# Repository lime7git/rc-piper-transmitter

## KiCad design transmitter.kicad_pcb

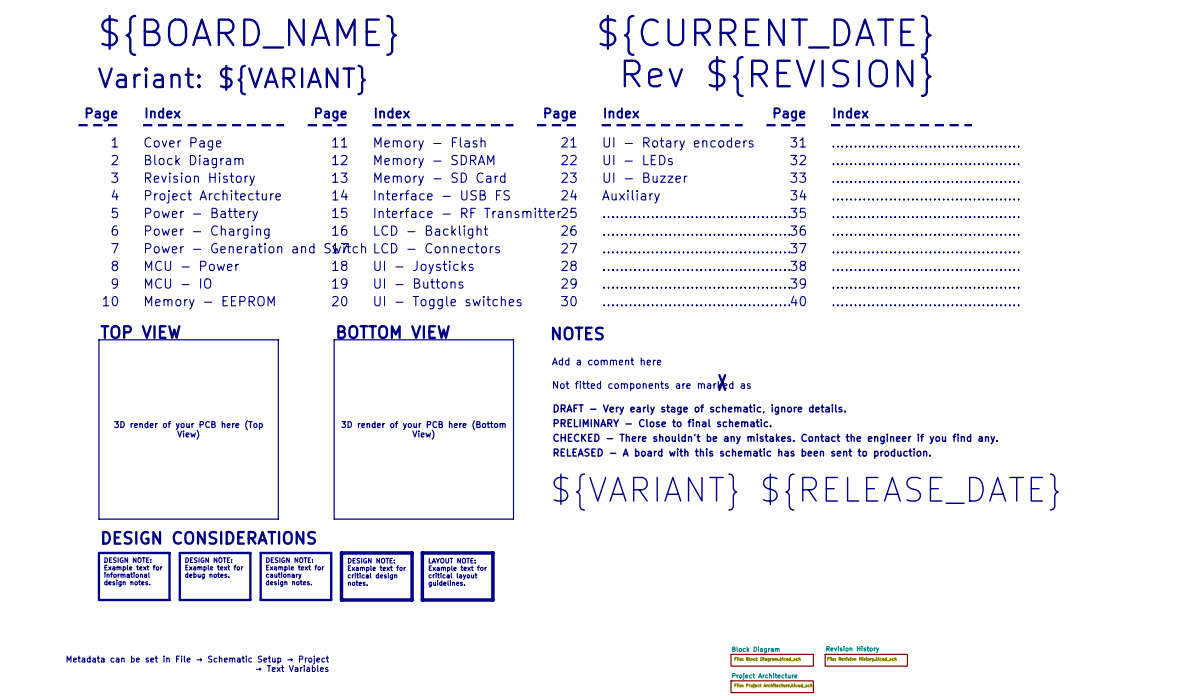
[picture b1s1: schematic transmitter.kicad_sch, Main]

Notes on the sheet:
BOTTOM VIEW
UI - Buzzer
RELEASED - A board with this schematic has been sent to production.
Page
TOP VIEW
Memory - EEPROM
MCU - IO
MCU - Power
LCD - Backlight
Not fitted components are marked as
...........................................
Index
Memory - SD Card
PRELIMINARY - Close to final schematic.
${VARIANT} ${RELEASE_DATE}
Project Architecture
${CURRENT_DATE}
Variant: ${VARIANT}
Rev ${REVISION}
Auxiliary
UI - LEDs
Power - Battery
UI - Buttons
Memory - Flash
LCD - Connectors
Interface - RF Transmitter
${BOARD_NAME}
DRAFT - Very early stage of schematic, ignore details.
Interface - USB FS
Power - Charging
Block Diagram
Add a comment here
UI - Joysticks
UI - Toggle switches
Cover Page
NOTES
Memory - SDRAM
Revision History
CHECKED - There shouldn't be any mistakes. Contact the engineer if you find any.
UI - Rotary encoders

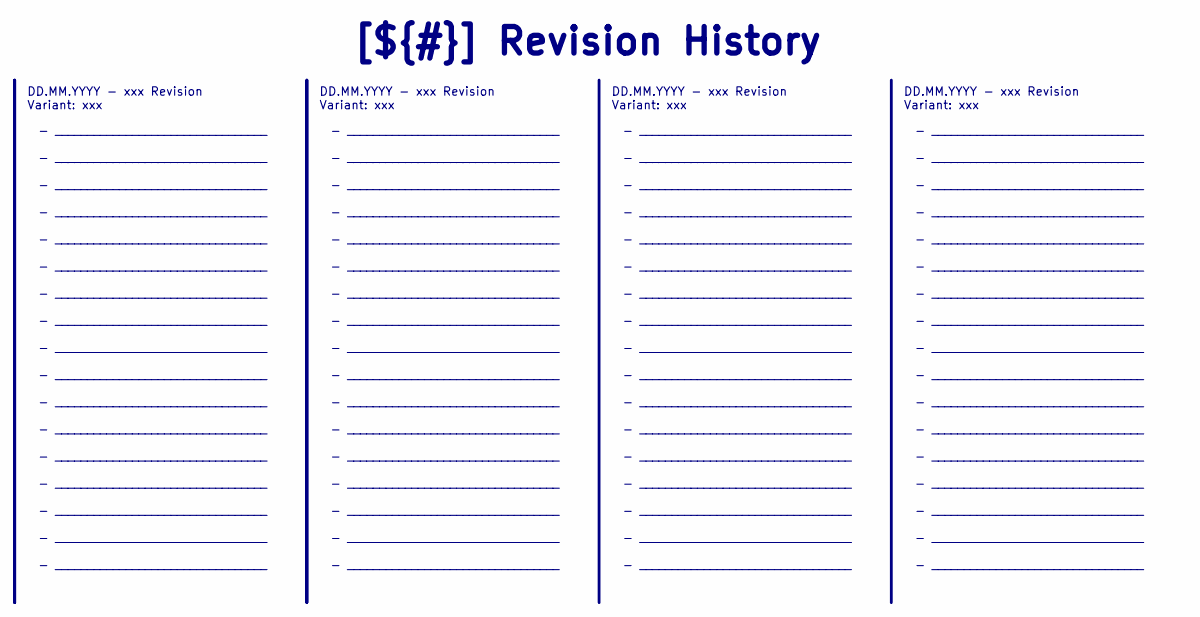
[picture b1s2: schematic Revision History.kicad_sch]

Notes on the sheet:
- _________________________________ - _________________________________ - _________________________________ - _________________________________ - _________________________________ - _________________________________ - _________________________________ - _________________________________ - _________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
DD.MM.YYYY - xxx Revision Variant: xxx
[${#}] ${TITLE}

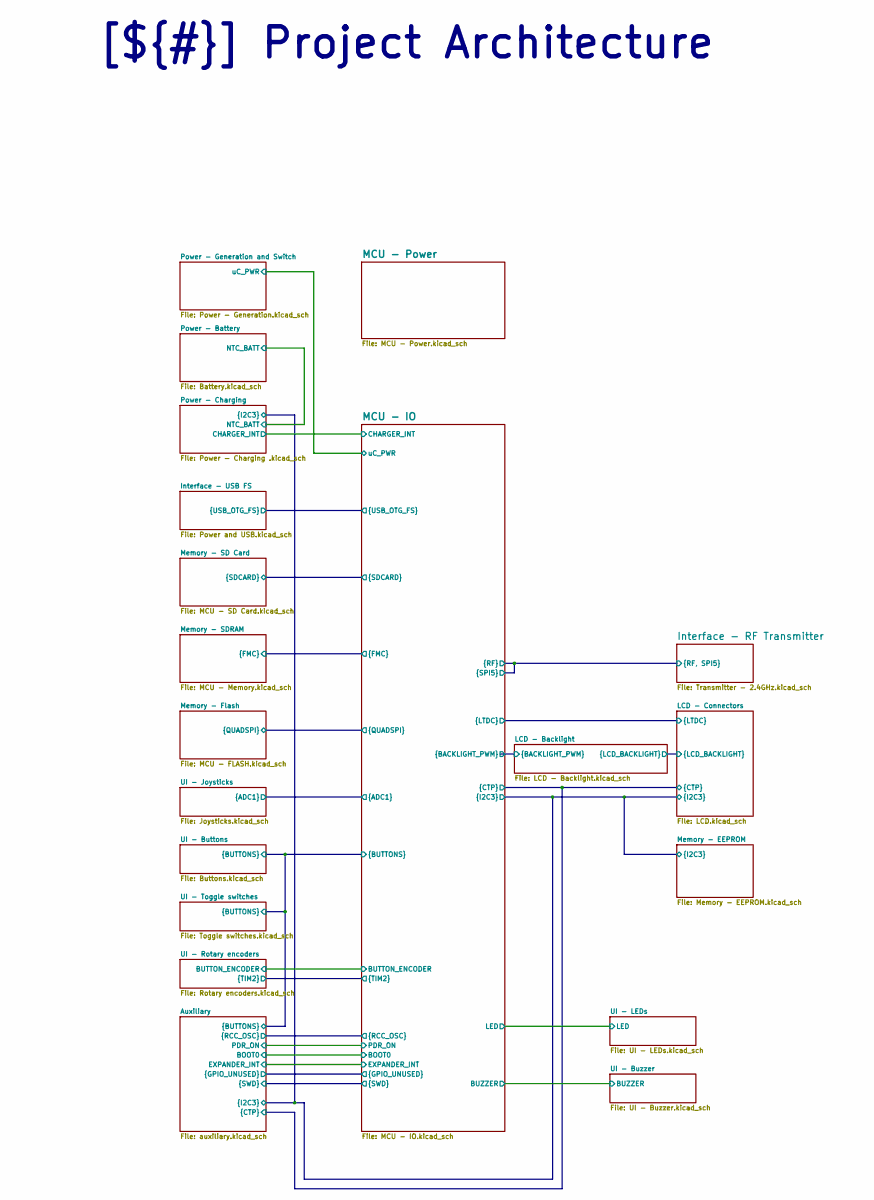
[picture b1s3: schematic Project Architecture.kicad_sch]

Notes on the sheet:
[${#}] ${TITLE}

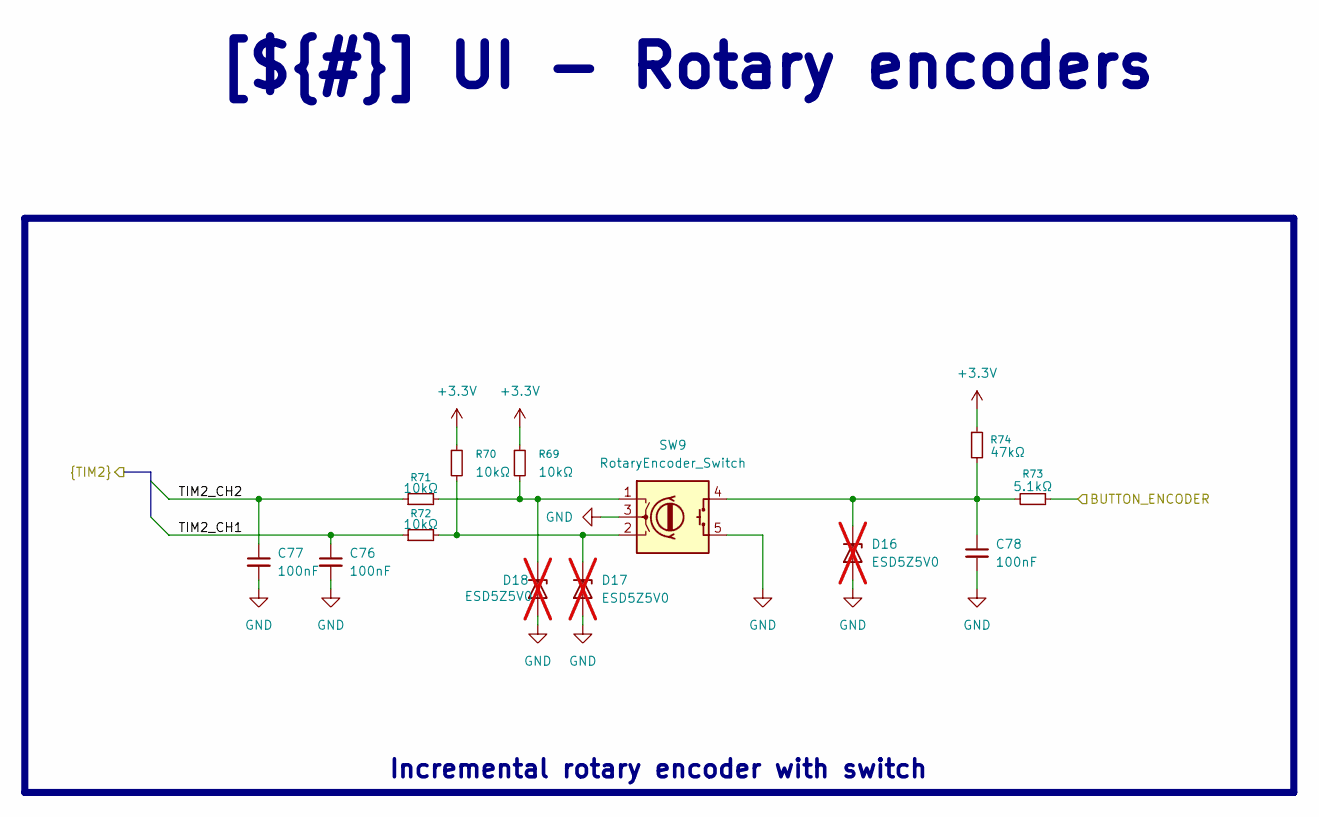
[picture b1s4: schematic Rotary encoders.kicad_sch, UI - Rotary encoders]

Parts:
C76, C77, C78: 100nF; C_0402_1005Metric
D16, D17, D18: ESD5Z5V0; D_SOD-523; not fitted
R69, R70, R71, R72: 10kΩ; R_0402_1005Metric
R73: 5.1kΩ; R_0402_1005Metric
R74: 47kΩ; R_0402_1005Metric
SW9: RotaryEncoder_Switch; JST_PH_B5B-PH-K_1x05_P2.00mm_Vertical

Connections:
+3.3V: R69.1, R70.1, R74.1; also elsewhere on the board
/Project Architecture/MCU - IO/ENC_BUTTON: R73.1; also elsewhere on the board
/Project Architecture/MCU - IO/TIM2_CH1: C76.1, R72.1; also elsewhere on the board
/Project Architecture/MCU - IO/TIM2_CH2: C77.1, R71.1; also elsewhere on the board
GND: C76.2, C77.2, C78.2, D16.2 (A), D17.2 (A), D18.2 (A), SW9.3, SW9.5; also elsewhere on the board
unnamed: C78.1, D16.1 (K), R73.2, R74.2, SW9.4
unnamed: D17.1 (K), R70.2, R72.2, SW9.2
unnamed: D18.1 (K), R69.2, R71.2, SW9.1

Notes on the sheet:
Incremental rotary encoder with switch
[${#}] ${TITLE}

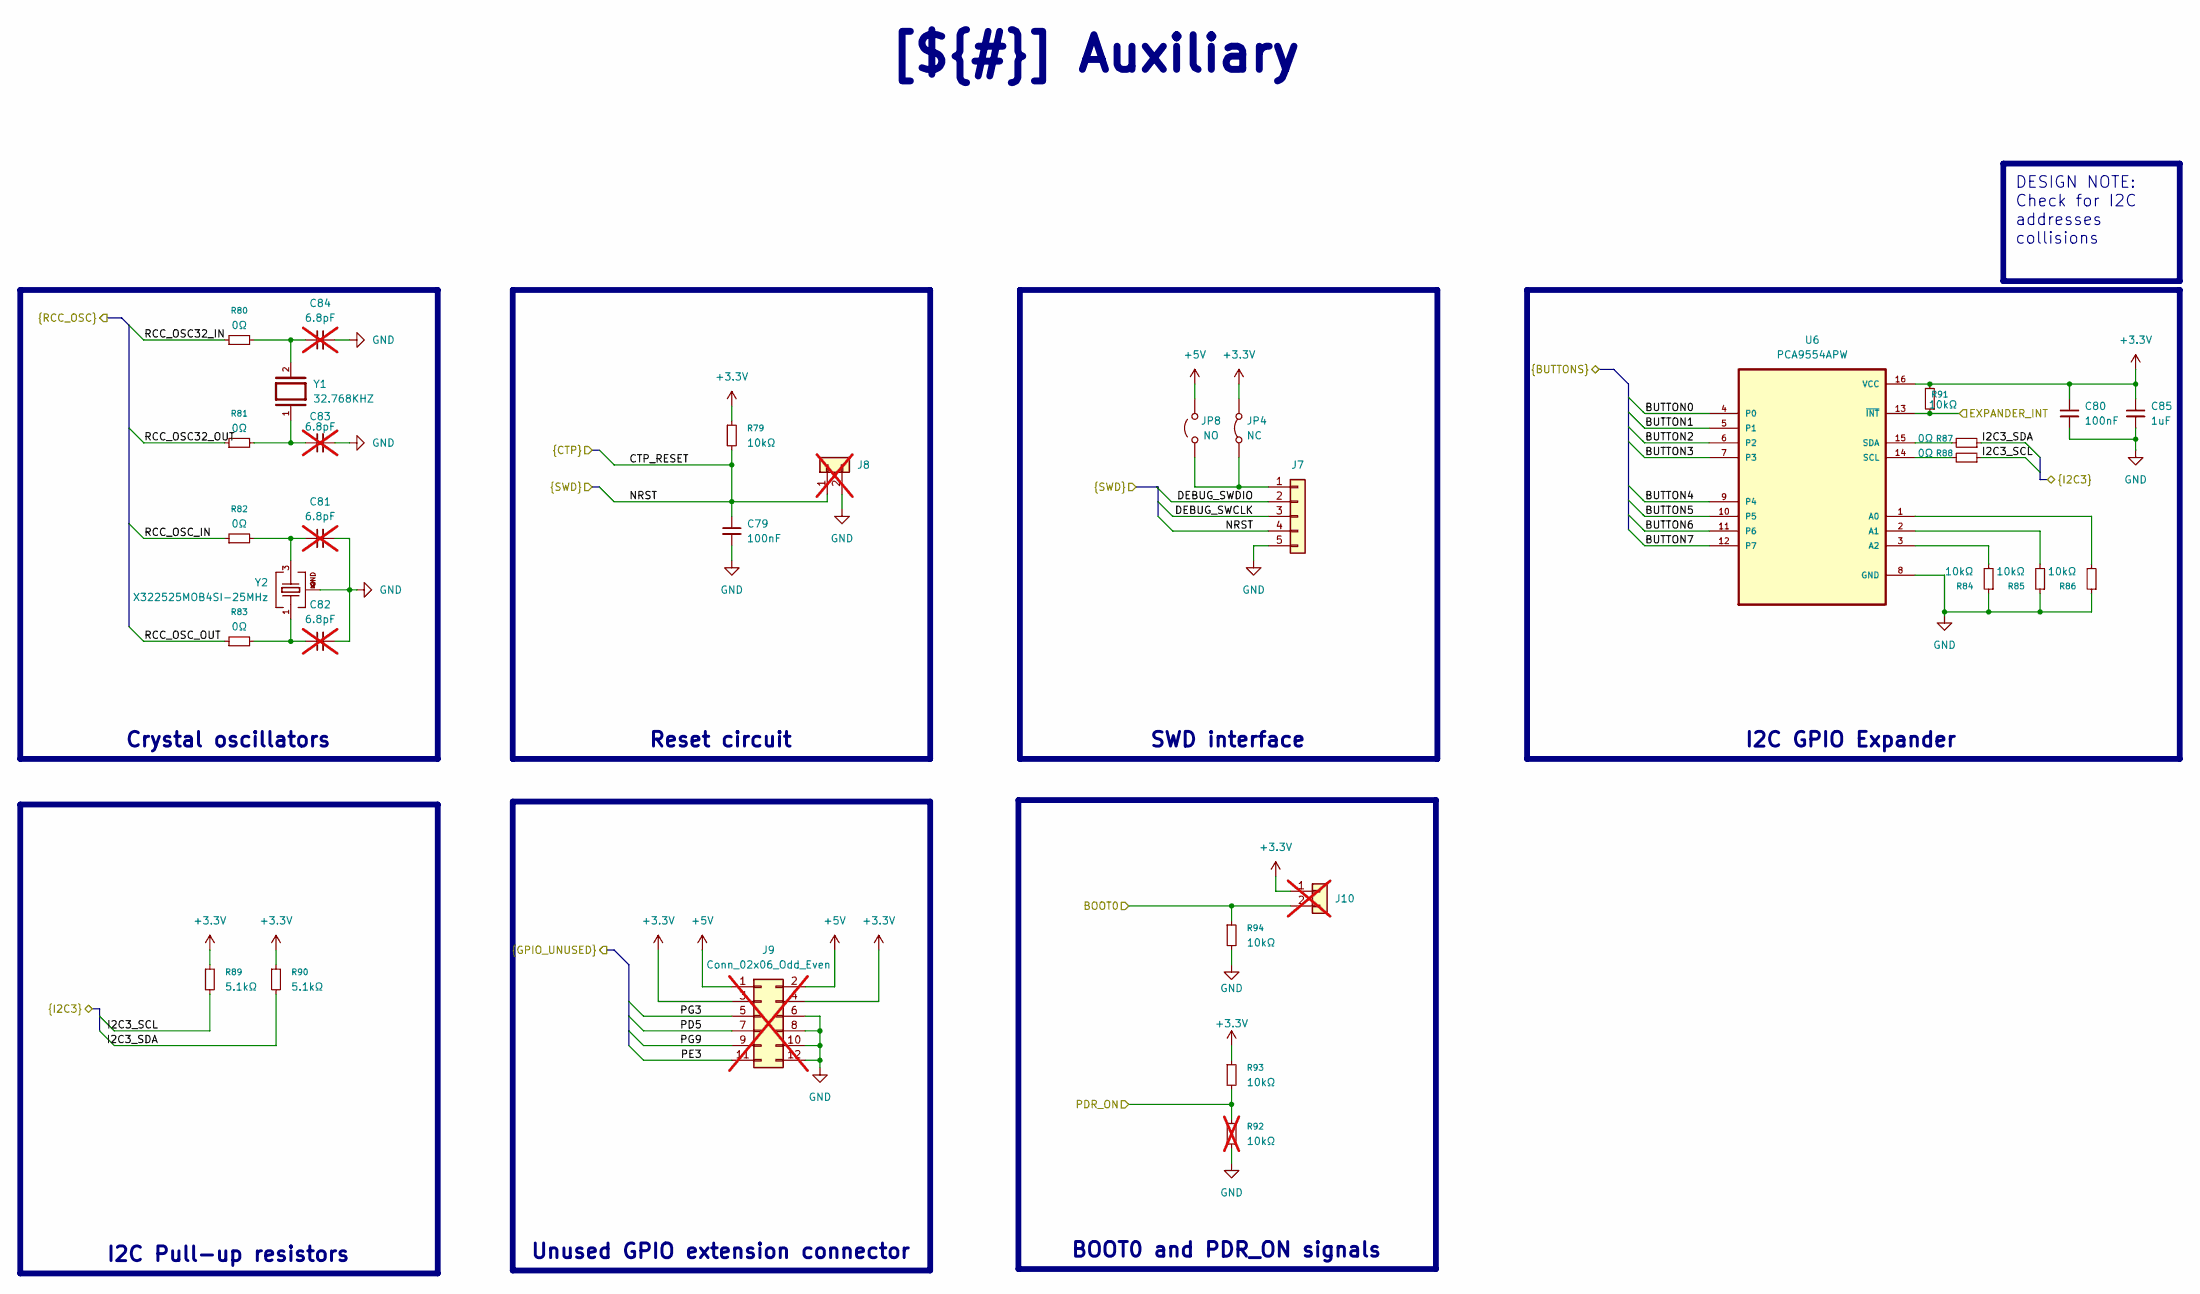
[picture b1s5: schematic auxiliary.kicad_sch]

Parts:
C79, C80: 100nF; C_0402_1005Metric
C81, C82, C83, C84: 6.8pF; C_0402_1005Metric; not fitted
C85: 1uF; C_0603_1608Metric
J7: Conn_01x05; JST_PH_B5B-PH-K_1x05_P2.00mm_Vertical
J8, J10: PinHeader_1x02_P2.00mm_Vertical; not fitted
J9: Conn_02x06_Odd_Even; PinSocket_2x06_P2.54mm_Vertical; not fitted
JP4: NC; SolderJumper-2_P1.3mm_Open_TrianglePad1.0x1.5mm
JP8: NO; SolderJumper-2_P1.3mm_Open_TrianglePad1.0x1.5mm
R79, R84, R85, R86, R91, R93, R94: 10kΩ; R_0402_1005Metric
R80, R81, R82, R83, R87, R88: 0Ω; R_0402_1005Metric
R89, R90: 5.1kΩ; R_0402_1005Metric
R92: 10kΩ; R_0402_1005Metric; not fitted
U6: PCA9554APW; SOP65P640X120-16N
Y1: 32.768KHZ; Q13FC13500004-32.768KHZ-4-T; PARTREV 08.19.15
Y2: X322525MOB4SI-25MHz; X322525MOB4SI 25MHz

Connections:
+3.3V: C80.1, C85.1, J9.3, J9.4, J10.1, JP4.2 (B), R79.1, R89.1, R90.1, R91.2, R93.1, U6.16 (VCC); also elsewhere on the board
+5V: J9.1, J9.2, JP8.1 (A); also elsewhere on the board
/Project Architecture/Auxiliary/BUTTON0: U6.4 (P0); also elsewhere on the board
/Project Architecture/Auxiliary/BUTTON1: U6.5 (P1); also elsewhere on the board
/Project Architecture/Auxiliary/BUTTON2: U6.6 (P2); also elsewhere on the board
/Project Architecture/Auxiliary/BUTTON3: U6.7 (P3); also elsewhere on the board
/Project Architecture/Auxiliary/BUTTON4: U6.9 (P4); also elsewhere on the board
/Project Architecture/Auxiliary/BUTTON5: U6.10 (P5); also elsewhere on the board
/Project Architecture/Auxiliary/BUTTON6: U6.11 (P6); also elsewhere on the board
/Project Architecture/Auxiliary/BUTTON7: U6.12 (P7); also elsewhere on the board
/Project Architecture/Auxiliary/DEBUG_SWCLK: J7.3; also elsewhere on the board
/Project Architecture/Auxiliary/DEBUG_SWDIO: J7.2; also elsewhere on the board
/Project Architecture/Auxiliary/I2C3_SCL: R88.1, R89.2; also elsewhere on the board
/Project Architecture/Auxiliary/I2C3_SDA: R87.1, R90.2; also elsewhere on the board
/Project Architecture/Auxiliary/NRST: C79.1, J7.4, J8.1, R79.2; also elsewhere on the board
/Project Architecture/Auxiliary/PD5: J9.7; also elsewhere on the board
/Project Architecture/Auxiliary/PE3: J9.11; also elsewhere on the board
/Project Architecture/Auxiliary/PG3: J9.5; also elsewhere on the board
/Project Architecture/Auxiliary/PG9: J9.9; also elsewhere on the board
/Project Architecture/Auxiliary/RCC_OSC32_IN: R80.1; also elsewhere on the board
/Project Architecture/Auxiliary/RCC_OSC32_OUT: R81.1; also elsewhere on the board
/Project Architecture/Auxiliary/RCC_OSC_IN: R82.1; also elsewhere on the board
/Project Architecture/Auxiliary/RCC_OSC_OUT: R83.1; also elsewhere on the board
/Project Architecture/MCU - IO/BOOT0: J10.2, R94.1; also elsewhere on the board
/Project Architecture/MCU - IO/EXPANDER_INT: R91.1, U6.13 (~INT); also elsewhere on the board
/Project Architecture/MCU - IO/PDR_ON: R92.1, R93.2; also elsewhere on the board
GND: C79.2, C80.2, C81.2, C82.2, C83.2, C84.2, C85.2, J7.5, J8.2, J9.6, J9.8, J9.10, J9.12, R84.1, R85.1, R86.1, R92.2, R94.2, U6.8 (GND), Y2.2, Y2.4; also elsewhere on the board
unnamed: C81.1, R82.2, Y2.3
unnamed: C82.1, R83.2, Y2.1
unnamed: C83.1, R81.2, Y1.1
unnamed: C84.1, R80.2, Y1.2
unnamed: J7.1, JP4.1 (A), JP8.2 (B)
unnamed: R86.2, U6.1 (A0)
unnamed: R85.2, U6.2 (A1)
unnamed: R84.2, U6.3 (A2)
unnamed: R88.2, U6.14 (SCL)
unnamed: R87.2, U6.15 (SDA)

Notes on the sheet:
Reset circuit
[${#}] ${TITLE}
BOOT0 and PDR_ON signals
I2C GPIO Expander
DESIGN NOTE: Check for I2C addresses collisions
I2C Pull-up resistors
Crystal oscillators
SWD interface
Unused GPIO extension connector

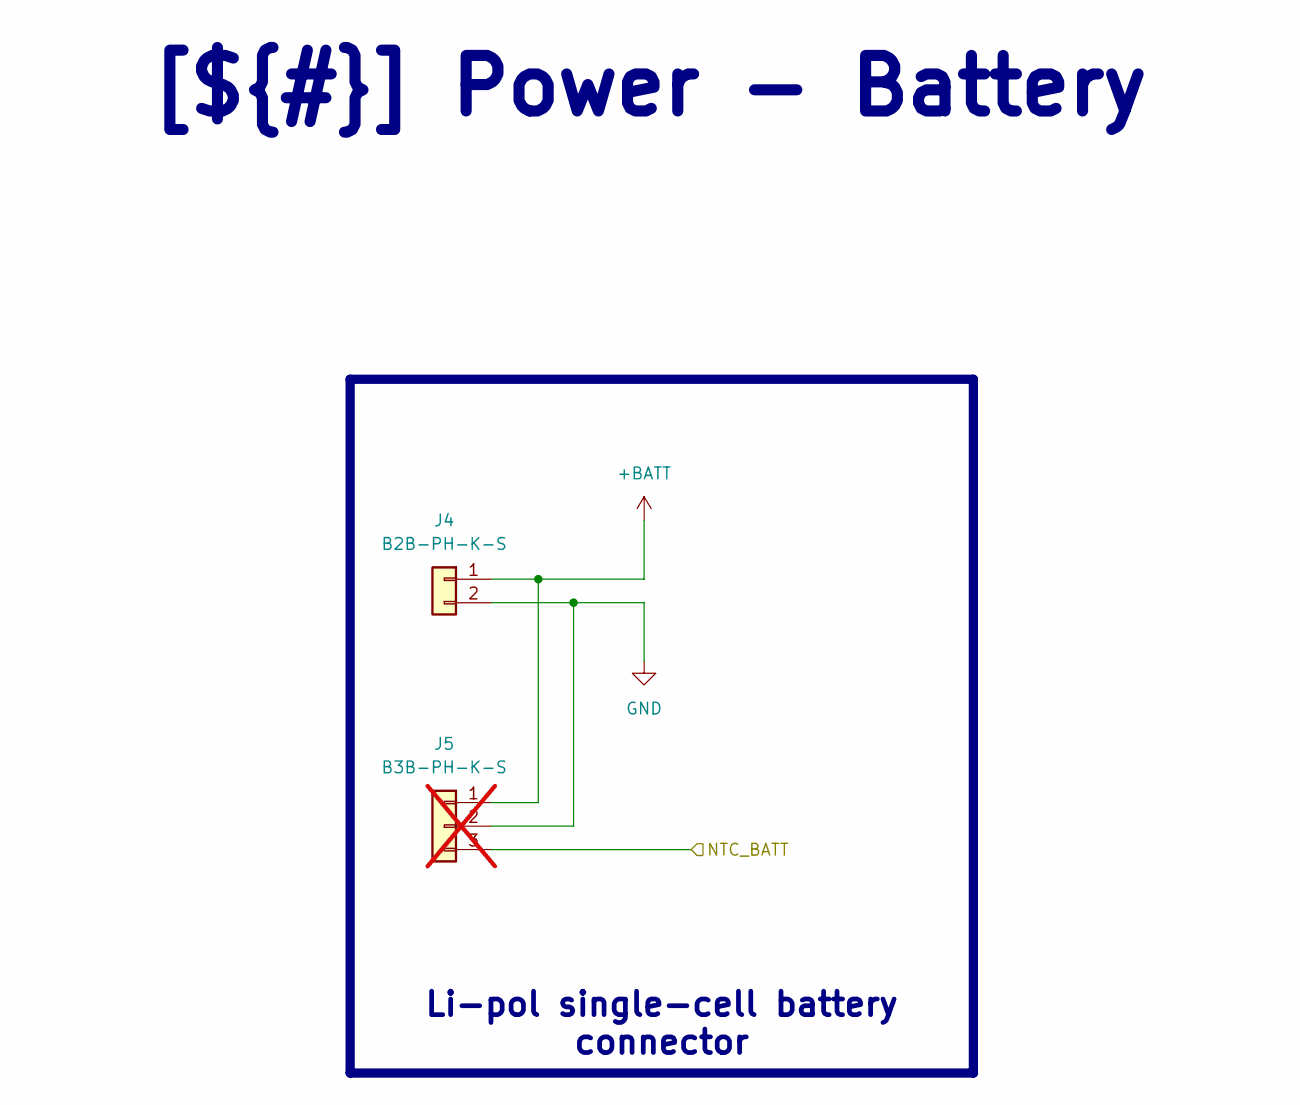
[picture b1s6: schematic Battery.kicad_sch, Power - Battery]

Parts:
J4: B2B-PH-K-S; JST_PH_B2B-PH-K_1x02_P2.00mm_Vertical
J5: B3B-PH-K-S; JST_PH_B3B-PH-K_1x03_P2.00mm_Vertical; not fitted

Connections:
+BATT: J4.1, J5.1; also elsewhere on the board
/Project Architecture/Power - Battery/NTC_BATT: J5.3 (Pin_2); also elsewhere on the board
GND: J4.2, J5.2; also elsewhere on the board

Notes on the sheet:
Li-pol single-cell battery connector
[${#}] ${TITLE}

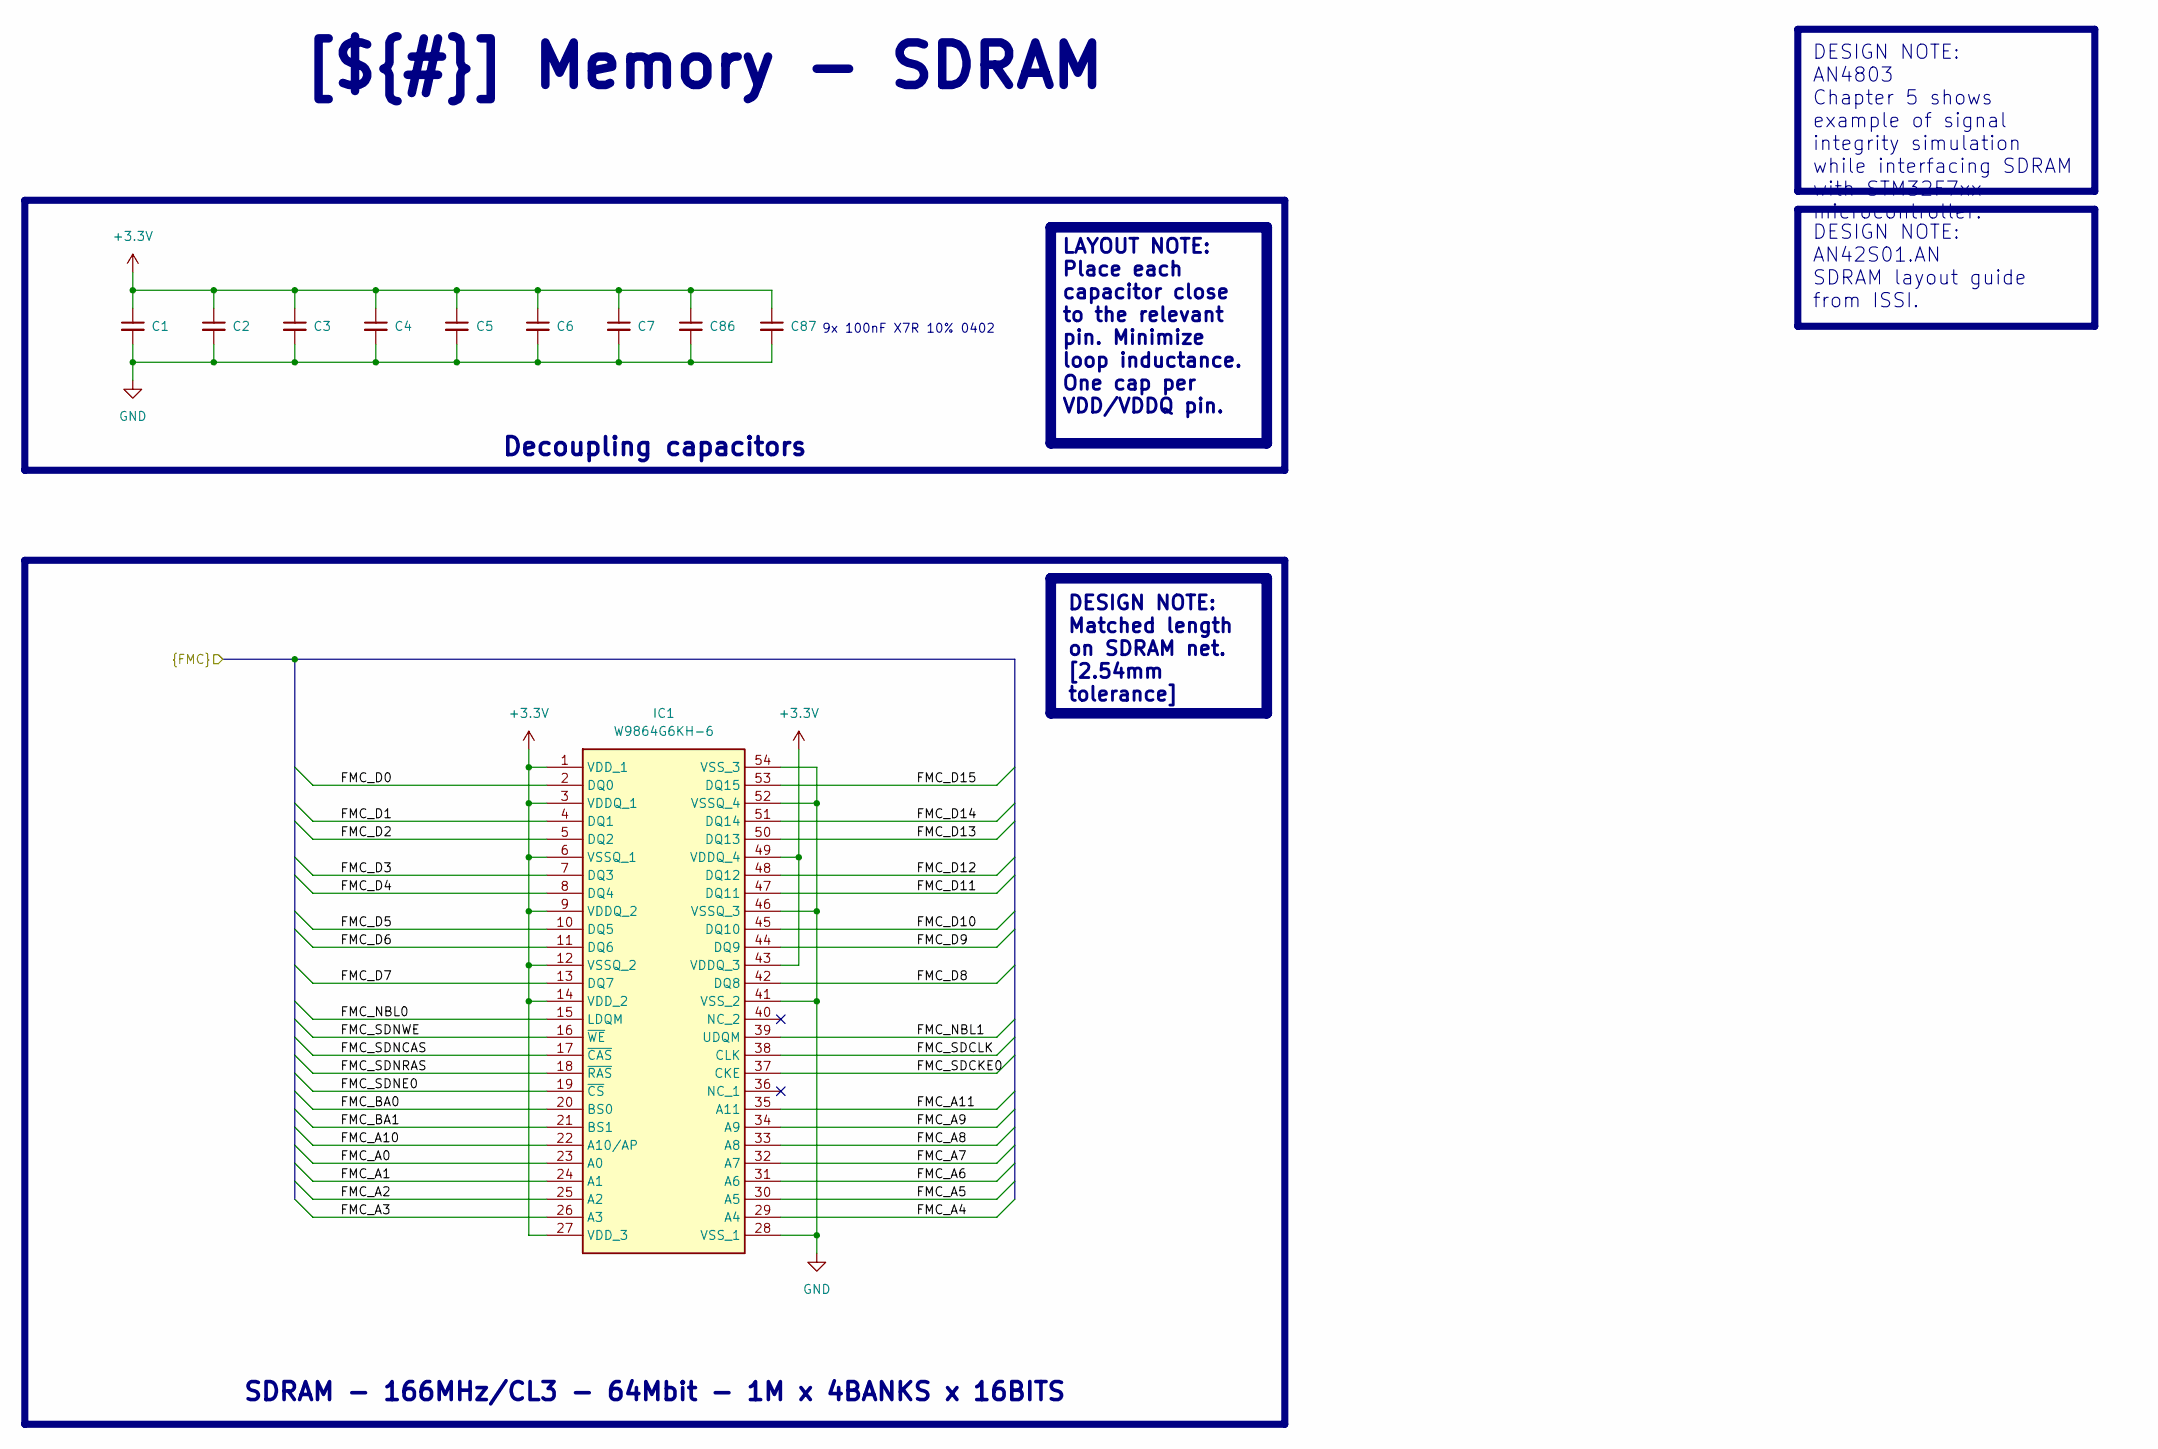
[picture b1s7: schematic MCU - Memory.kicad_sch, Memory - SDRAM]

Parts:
C1, C2, C3, C4, C5, C6, C7, C86, C87: 100nF; C_0402_1005Metric
IC1: W9864G6KH-6; SOP80P1176X120-54N; Mouser Part Number 454-W9864G6KH-6

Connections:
+3.3V: C1.1, C2.1, C3.1, C4.1, C5.1, C6.1, C7.1, C86.1, C87.1, IC1.1 (VDD_1), IC1.3 (VDDQ_1), IC1.6 (VSSQ_1), IC1.9 (VDDQ_2), IC1.12 (VSSQ_2), IC1.14 (VDD_2), IC1.27 (VDD_3), IC1.43 (VDDQ_3), IC1.49 (VDDQ_4); also elsewhere on the board
/Project Architecture/MCU - IO/FMC_A0: IC1.23 (A0); also elsewhere on the board
/Project Architecture/MCU - IO/FMC_A1: IC1.24 (A1); also elsewhere on the board
/Project Architecture/MCU - IO/FMC_A2: IC1.25 (A2); also elsewhere on the board
/Project Architecture/MCU - IO/FMC_A3: IC1.26 (A3); also elsewhere on the board
/Project Architecture/MCU - IO/FMC_A4: IC1.29 (A4); also elsewhere on the board
/Project Architecture/MCU - IO/FMC_A5: IC1.30 (A5); also elsewhere on the board
/Project Architecture/MCU - IO/FMC_A6: IC1.31 (A6); also elsewhere on the board
/Project Architecture/MCU - IO/FMC_A7: IC1.32 (A7); also elsewhere on the board
/Project Architecture/MCU - IO/FMC_A8: IC1.33 (A8); also elsewhere on the board
/Project Architecture/MCU - IO/FMC_A9: IC1.34 (A9); also elsewhere on the board
/Project Architecture/MCU - IO/FMC_A10: IC1.22 (A10/AP); also elsewhere on the board
/Project Architecture/MCU - IO/FMC_A11: IC1.35 (A11); also elsewhere on the board
/Project Architecture/MCU - IO/FMC_BA0: IC1.20 (BS0); also elsewhere on the board
/Project Architecture/MCU - IO/FMC_BA1: IC1.21 (BS1); also elsewhere on the board
/Project Architecture/MCU - IO/FMC_D0: IC1.2 (DQ0); also elsewhere on the board
/Project Architecture/MCU - IO/FMC_D1: IC1.4 (DQ1); also elsewhere on the board
/Project Architecture/MCU - IO/FMC_D2: IC1.5 (DQ2); also elsewhere on the board
/Project Architecture/MCU - IO/FMC_D3: IC1.7 (DQ3); also elsewhere on the board
/Project Architecture/MCU - IO/FMC_D4: IC1.8 (DQ4); also elsewhere on the board
/Project Architecture/MCU - IO/FMC_D5: IC1.10 (DQ5); also elsewhere on the board
/Project Architecture/MCU - IO/FMC_D6: IC1.11 (DQ6); also elsewhere on the board
/Project Architecture/MCU - IO/FMC_D7: IC1.13 (DQ7); also elsewhere on the board
/Project Architecture/MCU - IO/FMC_D8: IC1.42 (DQ8); also elsewhere on the board
/Project Architecture/MCU - IO/FMC_D9: IC1.44 (DQ9); also elsewhere on the board
/Project Architecture/MCU - IO/FMC_D10: IC1.45 (DQ10); also elsewhere on the board
/Project Architecture/MCU - IO/FMC_D11: IC1.47 (DQ11); also elsewhere on the board
/Project Architecture/MCU - IO/FMC_D12: IC1.48 (DQ12); also elsewhere on the board
/Project Architecture/MCU - IO/FMC_D13: IC1.50 (DQ13); also elsewhere on the board
/Project Architecture/MCU - IO/FMC_D14: IC1.51 (DQ14); also elsewhere on the board
/Project Architecture/MCU - IO/FMC_D15: IC1.53 (DQ15); also elsewhere on the board
/Project Architecture/MCU - IO/FMC_NBL0: IC1.15 (LDQM); also elsewhere on the board
/Project Architecture/MCU - IO/FMC_NBL1: IC1.39 (UDQM); also elsewhere on the board
/Project Architecture/MCU - IO/FMC_SDCKE0: IC1.37 (CKE); also elsewhere on the board
/Project Architecture/MCU - IO/FMC_SDCLK: IC1.38 (CLK); also elsewhere on the board
/Project Architecture/MCU - IO/FMC_SDNCAS: IC1.17 (~CAS); also elsewhere on the board
/Project Architecture/MCU - IO/FMC_SDNE0: IC1.19 (~CS); also elsewhere on the board
/Project Architecture/MCU - IO/FMC_SDNRAS: IC1.18 (~RAS); also elsewhere on the board
/Project Architecture/MCU - IO/FMC_SDNWE: IC1.16 (~WE); also elsewhere on the board
GND: C1.2, C2.2, C3.2, C4.2, C5.2, C6.2, C7.2, C86.2, C87.2, IC1.28 (VSS_1), IC1.41 (VSS_2), IC1.46 (VSSQ_3), IC1.52 (VSSQ_4), IC1.54 (VSS_3); also elsewhere on the board

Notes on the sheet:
9x 100nF X7R 10% 0402
DESIGN NOTE: Matched length on SDRAM net. [2.54mm tolerance]
SDRAM - 166MHz/CL3 - 64Mbit - 1M x 4BANKS x 16BITS
[${#}] ${TITLE}
DESIGN NOTE: AN4803 Chapter 5 shows example of signal integrity simulation while interfacing SDRAM with STM32F7xx microcontroller.
LAYOUT NOTE: Place each capacitor close to the relevant pin. Minimize loop inductance. One cap per VDD/VDDQ pin.
DESIGN NOTE: AN42S01.AN SDRAM layout guide from ISSI.
Decoupling capacitors

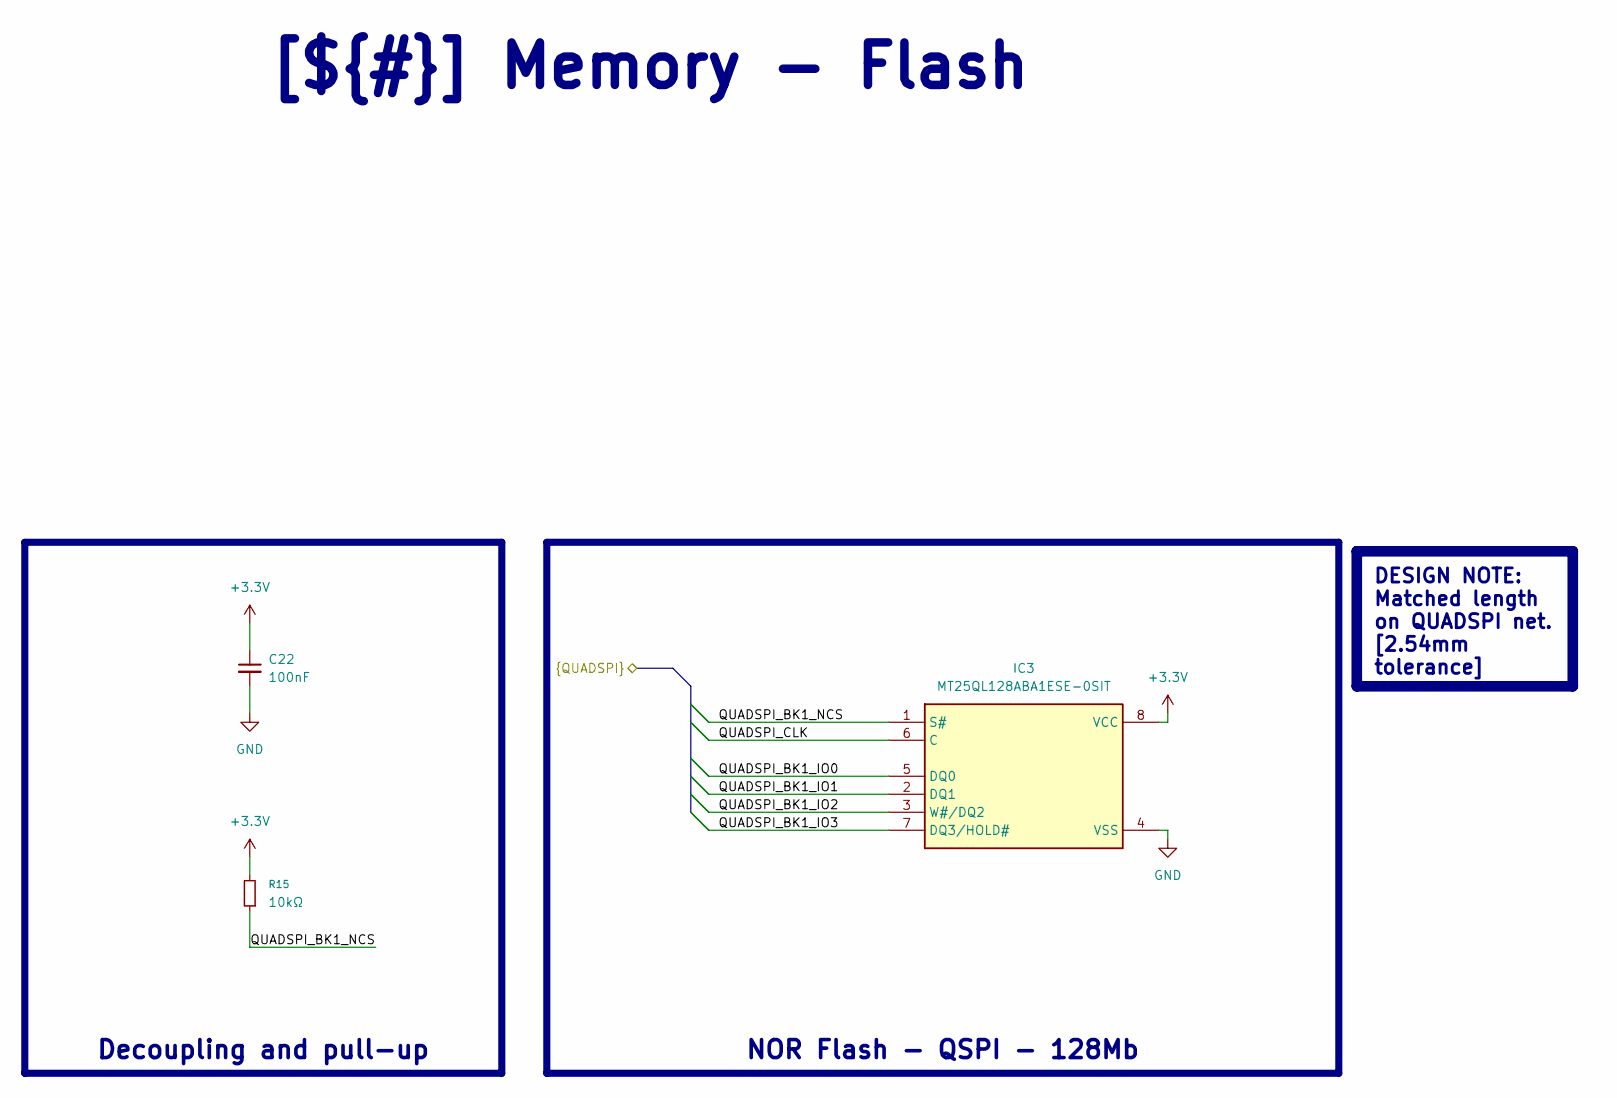
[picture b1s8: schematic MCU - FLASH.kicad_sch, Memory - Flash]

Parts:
C22: 100nF; C_0402_1005Metric
IC3: MT25QL128ABA1ESE-0SIT; SOIC127P790X216-8L; Mouser Part Number 340-224871-TRAY
R15: 10kΩ; R_0402_1005Metric

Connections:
+3.3V: C22.1, IC3.8 (VCC), R15.2; also elsewhere on the board
/Project Architecture/MCU - IO/QUADSPI_BK1_IO0: IC3.5 (DQ0); also elsewhere on the board
/Project Architecture/MCU - IO/QUADSPI_BK1_IO1: IC3.2 (DQ1); also elsewhere on the board
/Project Architecture/MCU - IO/QUADSPI_BK1_IO2: IC3.3 (W#/DQ2); also elsewhere on the board
/Project Architecture/MCU - IO/QUADSPI_BK1_IO3: IC3.7 (DQ3/HOLD#); also elsewhere on the board
/Project Architecture/MCU - IO/QUADSPI_BK1_NCS: IC3.1 (S#), R15.1; also elsewhere on the board
/Project Architecture/MCU - IO/QUADSPI_CLK: IC3.6 (C); also elsewhere on the board
GND: C22.2, IC3.4 (VSS); also elsewhere on the board

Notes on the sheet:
NOR Flash - QSPI - 128Mb
DESIGN NOTE: Matched length on QUADSPI net. [2.54mm tolerance]
Decoupling and pull-up
[${#}] ${TITLE}

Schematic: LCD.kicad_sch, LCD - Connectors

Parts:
C9, C10, C11: 100nF; C_0402_1005Metric
C12, C13: 4.7uF; C_0805_2012Metric
J1: AFC07-S40ECA-00; Manufacturer_Part_Number AFC07-S40ECA-00
J11: AFC07-S10FCC-00; AFC07S10ECC00; Manufacturer_Part_Number AFC07-S10FCC-00
R7, R8: 10kΩ; R_0402_1005Metric

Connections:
+3.3V: C9.1, C10.1, C12.1, C13.1, J1.4, J11.10, R7.2, R8.2; also elsewhere on the board
/Project Architecture/Auxiliary/CTP_IRQ: J11.5, R8.1
/Project Architecture/Auxiliary/I2C3_SCL: J11.7; also elsewhere on the board
/Project Architecture/Auxiliary/I2C3_SDA: J11.6; also elsewhere on the board
/Project Architecture/Auxiliary/NRST: J11.3; also elsewhere on the board
/Project Architecture/LCD - Backlight/LCD_BACKLIGHT_V+: J1.2; also elsewhere on the board
/Project Architecture/LCD - Backlight/LCD_BACKLIGHT_V-: J1.1; also elsewhere on the board
/Project Architecture/LCD - Connectors/LCD_DISP: C11.1, J1.31, R7.1
/Project Architecture/LCD - Connectors/LTDC_B0: J1.21; also elsewhere on the board
/Project Architecture/LCD - Connectors/LTDC_B1: J1.22; also elsewhere on the board
/Project Architecture/LCD - Connectors/LTDC_B2: J1.23; also elsewhere on the board
/Project Architecture/LCD - Connectors/LTDC_B3: J1.24; also elsewhere on the board
/Project Architecture/LCD - Connectors/LTDC_B4: J1.25; also elsewhere on the board
/Project Architecture/LCD - Connectors/LTDC_B5: J1.26; also elsewhere on the board
/Project Architecture/LCD - Connectors/LTDC_B6: J1.27; also elsewhere on the board
/Project Architecture/LCD - Connectors/LTDC_B7: J1.28; also elsewhere on the board
/Project Architecture/LCD - Connectors/LTDC_CLK: J1.30; also elsewhere on the board
/Project Architecture/LCD - Connectors/LTDC_DE: J1.34; also elsewhere on the board
/Project Architecture/LCD - Connectors/LTDC_G0: J1.13; also elsewhere on the board
/Project Architecture/LCD - Connectors/LTDC_G1: J1.14; also elsewhere on the board
/Project Architecture/LCD - Connectors/LTDC_G2: J1.15; also elsewhere on the board
/Project Architecture/LCD - Connectors/LTDC_G3: J1.16; also elsewhere on the board
/Project Architecture/LCD - Connectors/LTDC_G4: J1.17; also elsewhere on the board
/Project Architecture/LCD - Connectors/LTDC_G5: J1.18; also elsewhere on the board
/Project Architecture/LCD - Connectors/LTDC_G6: J1.19; also elsewhere on the board
/Project Architecture/LCD - Connectors/LTDC_G7: J1.20; also elsewhere on the board
/Project Architecture/LCD - Connectors/LTDC_HSYNC: J1.32; also elsewhere on the board
/Project Architecture/LCD - Connectors/LTDC_R0: J1.5; also elsewhere on the board
/Project Architecture/LCD - Connectors/LTDC_R1: J1.6; also elsewhere on the board
/Project Architecture/LCD - Connectors/LTDC_R2: J1.7; also elsewhere on the board
/Project Architecture/LCD - Connectors/LTDC_R3: J1.8; also elsewhere on the board
/Project Architecture/LCD - Connectors/LTDC_R4: J1.9; also elsewhere on the board
/Project Architecture/LCD - Connectors/LTDC_R5: J1.10; also elsewhere on the board
/Project Architecture/LCD - Connectors/LTDC_R6: J1.11; also elsewhere on the board
/Project Architecture/LCD - Connectors/LTDC_R7: J1.12; also elsewhere on the board
/Project Architecture/LCD - Connectors/LTDC_VSYNC: J1.33; also elsewhere on the board
GND: C9.2, C10.2, C11.2, C12.2, C13.2, J1.3, J1.29, J1.36, J11.4, J11.8, J11.9; also elsewhere on the board

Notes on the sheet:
Decoupling and pull-up
LAYOUT NOTE: Decoupling capacitors, place close to connector.
LCD Touch Controller Connector - FFC 10pin 0.5mm pitch
[${#}] ${TITLE}
LCD Display Connector - FFC 40pin 0.5mm pitch
Decoupling and pull-up

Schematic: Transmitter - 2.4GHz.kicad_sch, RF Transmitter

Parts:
C19: 10uF 16V; CP_EIA-3216-18_Kemet-A
C20: 100nF; C_0402_1005Metric
C21: 4.7uF; C_0805_2012Metric
E01-2G4M27D1: DS1023-2*4SF11; PE01-ML01DP5; Manufacturer_Part_Number DS1023-2*4SF11
R13, R14: 10kΩ; R_0402_1005Metric

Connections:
+3.3V: C19.1, C20.1, C21.1, E01-2G4M27D1.2 (VCC), R13.2, R14.2; also elsewhere on the board
/Project Architecture/Interface - RF Transmitter/RF_CE: E01-2G4M27D1.3 (CE); also elsewhere on the board
/Project Architecture/Interface - RF Transmitter/RF_IRQ: E01-2G4M27D1.8 (IRQ), R14.1; also elsewhere on the board
/Project Architecture/Interface - RF Transmitter/SPI5_MISO: E01-2G4M27D1.7 (MISO); also elsewhere on the board
/Project Architecture/Interface - RF Transmitter/SPI5_MOSI: E01-2G4M27D1.6 (MOSI); also elsewhere on the board
/Project Architecture/Interface - RF Transmitter/SPI5_NSS: E01-2G4M27D1.4 (CSN), R13.1; also elsewhere on the board
/Project Architecture/Interface - RF Transmitter/SPI5_SCK: E01-2G4M27D1.5 (SCK); also elsewhere on the board
GND: C19.2, C20.2, C21.2, E01-2G4M27D1.1 (GND); also elsewhere on the board

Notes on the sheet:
Decoupling and pull-up
[${#}] ${TITLE}
LCD Touch Controller Connector - FFC 10pin 0.5mm pitch

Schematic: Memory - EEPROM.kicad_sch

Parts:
C8: 100nF; C_0402_1005Metric; not fitted
R1, R2, R3, R4: 10kΩ; R_0402_1005Metric; not fitted
R5, R6: 0Ω; R_0402_1005Metric; not fitted
U2: CAT24C256; SOIC-8_5.3x6.2mm_P1.27mm; not fitted

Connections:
+3.3V: C8.2, U2.8 (VCC); also elsewhere on the board
/Project Architecture/Auxiliary/I2C3_SCL: R6.2; also elsewhere on the board
/Project Architecture/Auxiliary/I2C3_SDA: R5.2; also elsewhere on the board
/Project Architecture/Memory - EEPROM/EEPROM_SCL: R6.1, U2.6 (SCL)
/Project Architecture/Memory - EEPROM/EEPROM_SDA: R5.1, U2.5 (SDA)
GND: C8.1, R1.2, R2.2, R3.2, R4.2, U2.4 (GND); also elsewhere on the board
unnamed: R1.1, U2.1 (A0)
unnamed: R2.1, U2.2 (A1)
unnamed: R3.1, U2.3 (A2)
unnamed: R4.1, U2.7 (WP)

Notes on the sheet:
EEPROM - I2C - 256Kbit
[${#}] ${TITLE}
